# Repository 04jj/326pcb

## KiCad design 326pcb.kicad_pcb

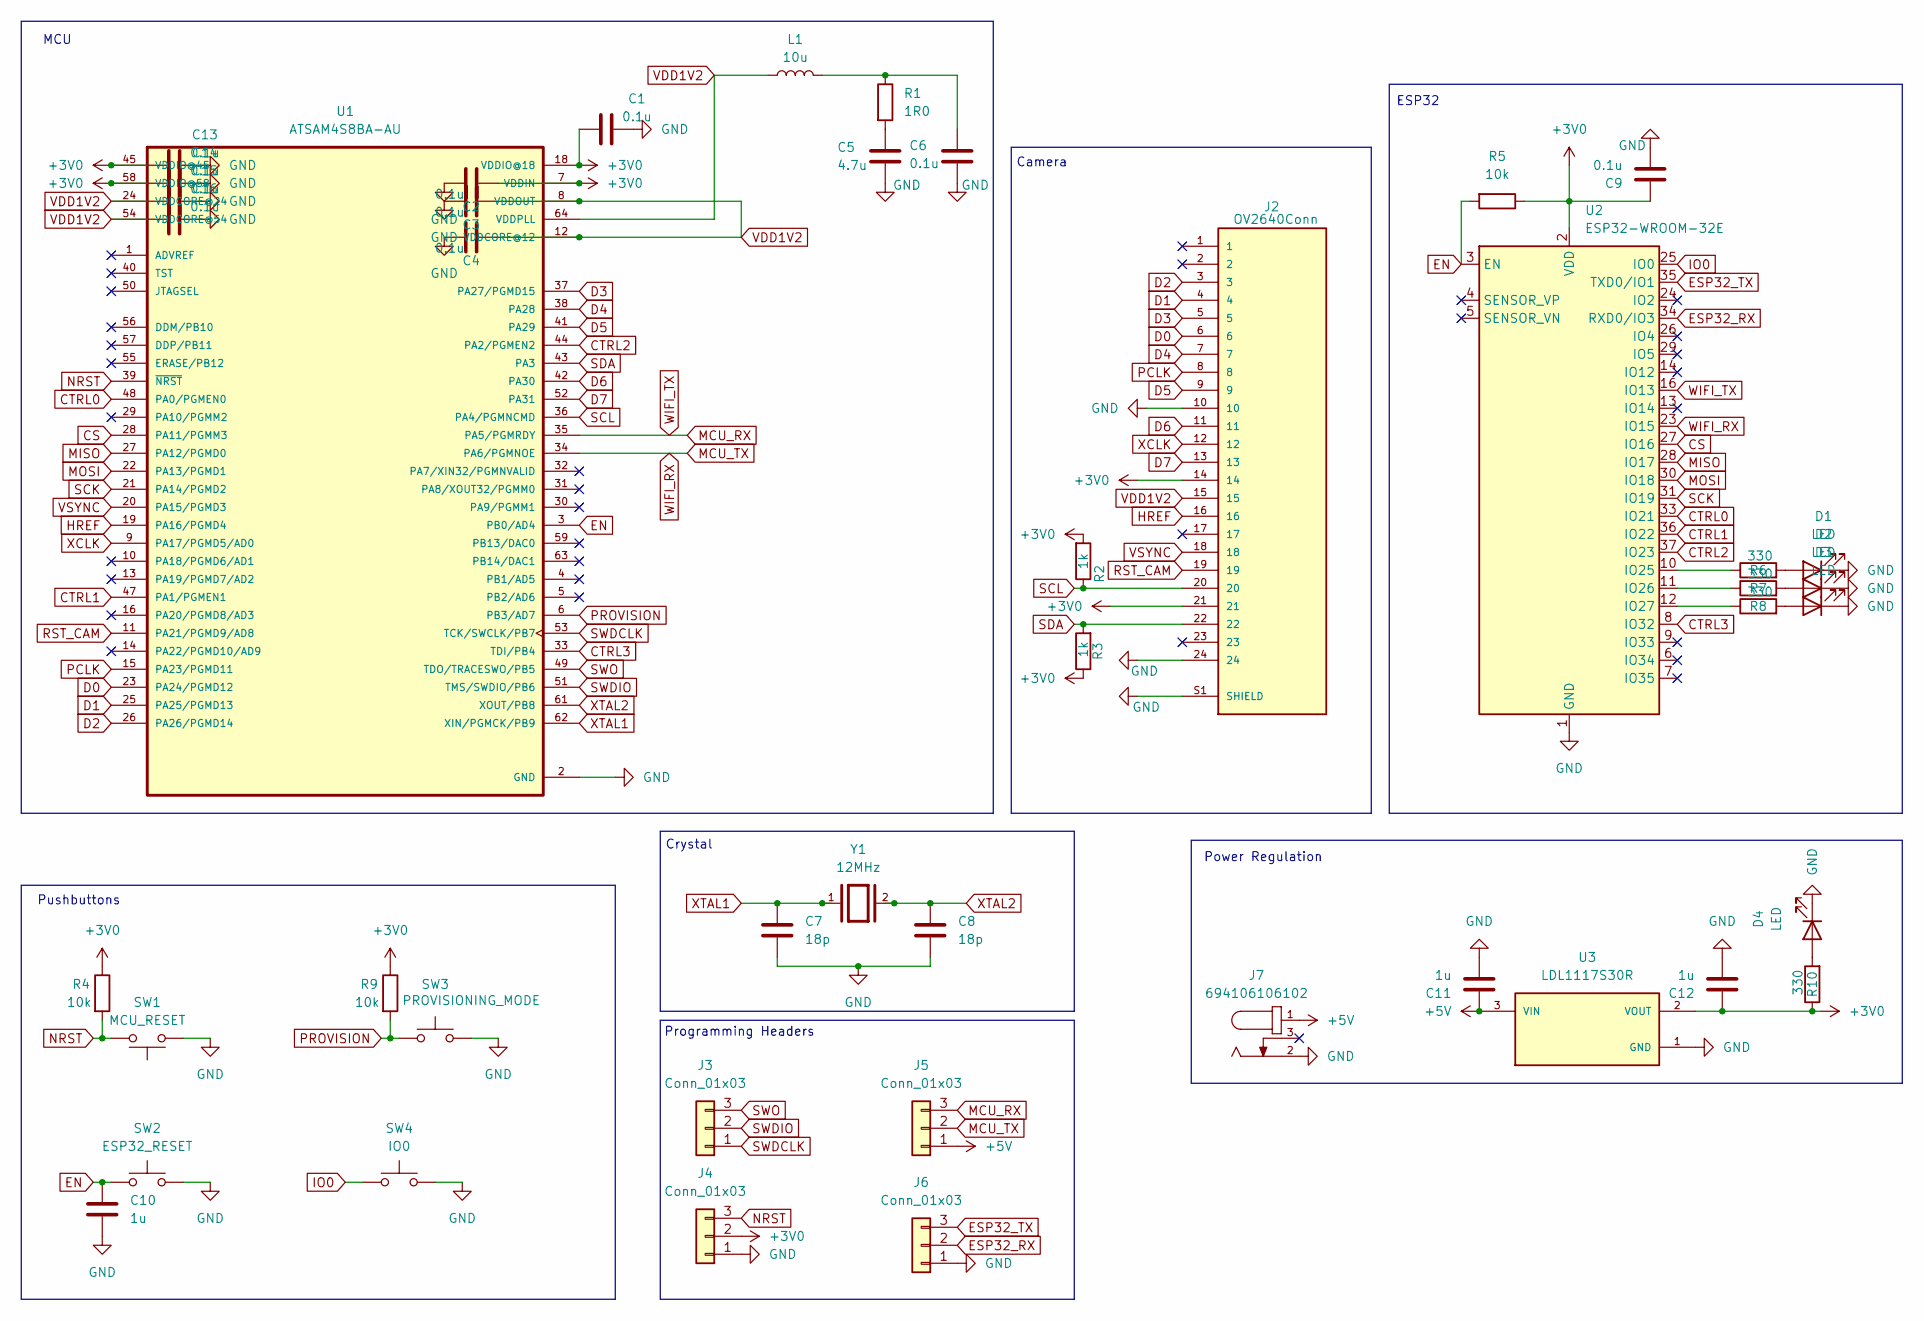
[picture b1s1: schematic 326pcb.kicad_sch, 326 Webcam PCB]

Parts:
C1, C2, C3, C4, C6, C9, C13, C14, C15, C16: 0.1u; C_0805_2012Metric
C5: 4.7u; C_0805_2012Metric
C7, C8: 18p; C_0805_2012Metric
C10, C11, C12: 1u; C_0805_2012Metric
D1, D2, D3, D4: LED; LED_0603_1608Metric
J2: OV2640Conn; TE_2-1734592-4; PARTREV C
J3, J4, J5, J6: Conn_01x03; PinHeader_1x03_P2.54mm_Vertical
J7: 694106106102
L1: 10u; L_0805_2012Metric
R1: 1R0; R_0805_2012Metric
R2, R3: 1k; R_0805_2012Metric
R4, R5, R9: 10k; R_0805_2012Metric
R6, R7, R8, R10: 330; R_0805_2012Metric
SW1: MCU_RESET; pushbutton
SW2: ESP32_RESET; pushbutton
SW3: PROVISIONING_MODE; pushbutton
SW4: IO0; pushbutton
U1: ATSAM4S8BA-AU; QFP50P1200X1200X160-64N; DIGI-KEY_PART_NUMBER ATSAM4S8BA-AU-ND
U2: ESP32-WROOM-32E
U3: LDL1117S30R; SOT230P700X180-4N; PARTREV 7
Y1: 12MHz; XTAL_ABM7-12.000MHZ-D2Y-T; PARTREV 9/3/2019

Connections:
+3V0: C1.1, C2.2, C9.1, C12.1, C13.1, C14.1, J2.14, J2.21, J4.2, R2.2, R3.1, R4.1, R5.1, R9.1, R10.1, U1.7 (VDDIN), U1.18 (VDDIO@18), U1.45 (VDDIO@45), U1.58 (VDDIO@58), U2.2 (VDD), U3.2 (VOUT), U3.4 (VOUT)
+5V: C11.1, J5.1, J7.1, J7.A1, U3.3 (VIN)
CS: U1.28 (PA11/PGMM3), U2.27 (IO16)
CTRL0: U1.48 (PA0/PGMEN0), U2.33 (IO21)
CTRL1: U1.47 (PA1/PGMEN1), U2.36 (IO22)
CTRL2: U1.44 (PA2/PGMEN2), U2.37 (IO23)
CTRL3: U1.33 (TDI/PB4), U2.8 (IO32)
D0: J2.6, U1.23 (PA24/PGMD12)
D1: J2.4, U1.25 (PA25/PGMD13)
D2: J2.3, U1.26 (PA26/PGMD14)
D3: J2.5, U1.37 (PA27/PGMD15)
D4: J2.7, U1.38 (PA28)
D5: J2.9, U1.41 (PA29)
D6: J2.11, U1.42 (PA30)
D7: J2.13, U1.52 (PA31)
EN: C10.1, R5.2, SW2.1, U1.3 (PB0/AD4), U2.3 (EN)
ESP32_RX: J6.2, U2.34 (RXD0/IO3)
ESP32_TX: J6.3, U2.35 (TXD0/IO1)
GND: C1.2, C2.1, C3.1, C4.1, C5.2, C6.2, C7.2, C8.2, C9.2, C10.2, C11.2, C12.2, C13.2, C14.2, C15.2, C16.2, D1.1 (K), D2.1 (K), D3.1 (K), D4.1 (K), J2.10, J2.24, J2.S1 (SHIELD), J2.S2 (SHIELD), J4.1, J6.1, J7.2, SW1.1, SW2.2, SW3.2, SW4.2, U1.2 (GND), U1.17 (GND), U1.46 (GND), U1.60 (GND), U2.1 (GND), U2.15 (GND), U2.38 (GND), U2.39 (GND), U3.1 (GND)
HREF: J2.16, U1.19 (PA16/PGMD4)
IO0: SW4.1, U2.25 (IO0)
MCU_RX: J5.3, U1.35 (PA5/PGMRDY), U2.16 (IO13)
MCU_TX: J5.2, U1.34 (PA6/PGMNOE), U2.23 (IO15)
MISO: U1.27 (PA12/PGMD0), U2.28 (IO17)
MOSI: U1.22 (PA13/PGMD1), U2.30 (IO18)
NRST: J4.3, R4.2, SW1.2, U1.39 (~NRST)
unnamed: C5.1, R1.2
unnamed: C6.1, L1.2, R1.1
unnamed: D1.2 (A), R6.2
unnamed: D2.2 (A), R7.2
unnamed: D3.2 (A), R8.2
unnamed: D4.2 (A), R10.2
unnamed: R6.1, U2.10 (IO25)
unnamed: R7.1, U2.11 (IO26)
unnamed: R8.1, U2.12 (IO27)
PCLK: J2.8, U1.15 (PA23/PGMD11)
PROVISION: R9.2, SW3.1, U1.6 (PB3/AD7)
RST_CAM: J2.19, U1.11 (PA21/PGMD9/AD8)
SCK: U1.21 (PA14/PGMD2), U2.31 (IO19)
SCL: J2.20, R2.1, U1.36 (PA4/PGMNCMD)
SDA: J2.22, R3.2, U1.43 (PA3)
SWDCLK: J3.1, U1.53 (TCK/SWCLK/PB7)
SWDIO: J3.2, U1.51 (TMS/SWDIO/PB6)
SWO: J3.3, U1.49 (TDO/TRACESWO/PB5)
VDD1V2: C3.2, C4.2, C15.1, C16.1, J2.15, L1.1, U1.8 (VDDOUT), U1.12 (VDDCORE@12), U1.24 (VDDCORE@24), U1.54 (VDDCORE@54), U1.64 (VDDPLL)
VSYNC: J2.18, U1.20 (PA15/PGMD3)
XCLK: J2.12, U1.9 (PA17/PGMD5/AD0)
XTAL1: C7.1, U1.62 (XIN/PGMCK/PB9), Y1.1
XTAL2: C8.1, U1.61 (XOUT/PB8), Y1.2

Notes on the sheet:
Programming Headers
Pushbuttons
Camera
Crystal
MCU
Power Regulation
ESP32

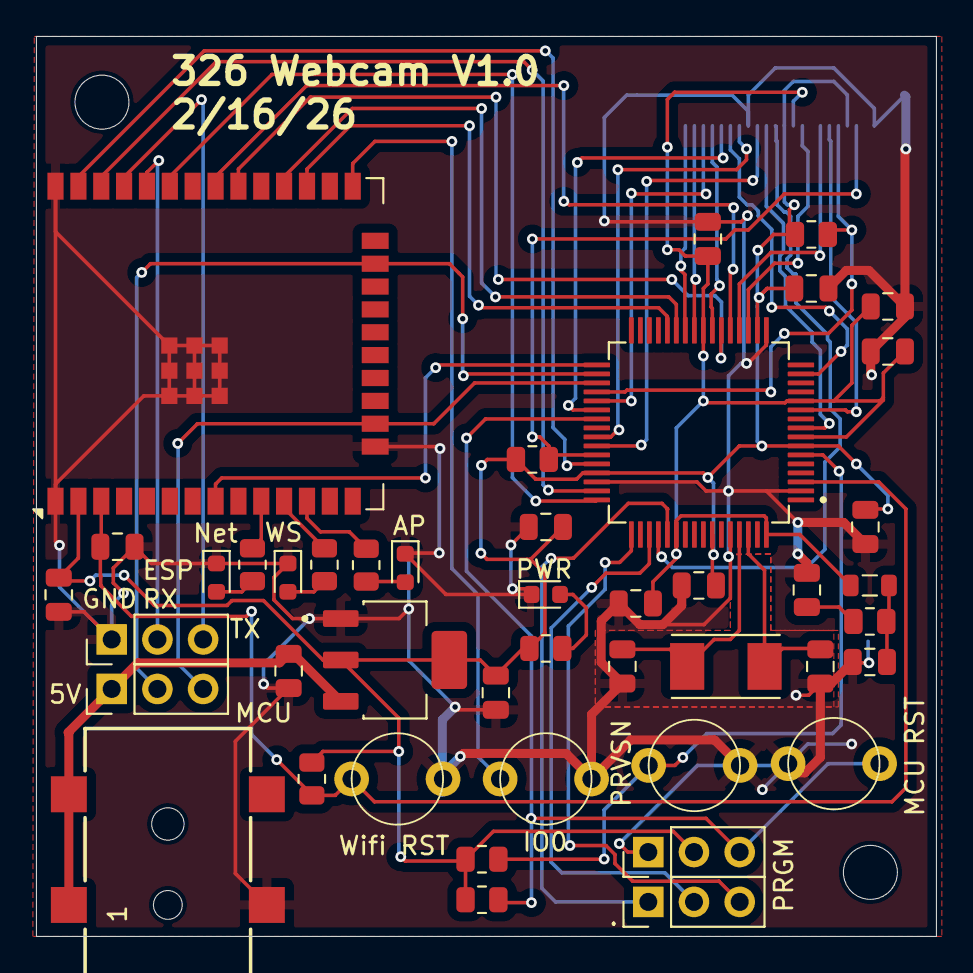
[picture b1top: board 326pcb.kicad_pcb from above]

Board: 2 copper layers, 50.0 x 50.0 mm, 45 parts (1 on the bottom side), 49 nets.

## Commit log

2026-02-17 Update files, Gerbers, Drill
2026-02-19 edit zip
2026-02-19 update pcb
